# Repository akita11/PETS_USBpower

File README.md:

# PETS_USBpower

[PETS](https://4ok.jp/pets/)をUSBモバイルバッテリで使えるように改造する部品です。

※PETSを分解・改造して使用します。そのため、PETSの製品保証の対象外となります。

# 用意するもの

※モバイルバッテリ以外の部材はスイッチサイエンスで委託販売予定です

* 筐体の板（2枚）：MDF板（厚さ2.5mm）をレーザーカッター等でカットします。（PETS_USBpower: PDFとInkscape SVGで同一内容）

* USBコネクタ：出っ張りが少ないUSBコネクタ（基板）。USBpowerconn_gerber.zipを基板製造サービス等で製造します（板厚は2.0mmとするか、1.6mmのものに裏面に厚紙などをはさんで厚さを調整する）※ケーブルが根本から切れやすいのでグルーガン等で強化したほうがいいです

* 電源ケーブル：JSTのXHコネクタ(2p)＋10cm程度のケーブル ※[aitendo](http://www.aitendo.com)で売っていることがある

* ダイソーで500円売っているUSBモバイルバッテリ（またはそれと同等のサイズのもの）。サイズは120mm x 70mm x 20mm程度以下であれば、収まります。

# 組み立て

[こちらの手順](https://github.com/akita11/PETS_USBpower/blob/master/instruction/README.md)で、PETSを分解・改造します。改造後は、普段どおりのPETSとして使用できます。

# おまけ

PETSblock_holder.{svg/pdf}をダンボール等でカットして組み立てると、PETSのブロックを保存しておくのに使えます。

# Author

Junichi Akita / @akita11 / akita@ifdl.jp

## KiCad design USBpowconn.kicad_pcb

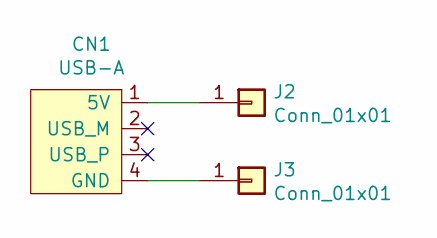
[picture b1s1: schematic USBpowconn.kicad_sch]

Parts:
CN1: USB-A; USB-A-PCB
J2, J3: Conn_01x01; PinSocket_1x01_P2.54mm_Vertical

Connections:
unnamed: CN1.1 (5V), J2.1
unnamed: CN1.4 (GND), J3.1

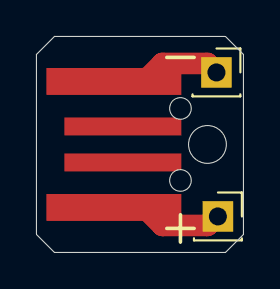
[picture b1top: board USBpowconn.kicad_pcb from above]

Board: 2 copper layers, 11.5 x 12.0 mm, 3 parts (0 on the bottom side), 2 nets.

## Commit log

2019-07-01 1st commit
2019-07-01 画像URLを修正
2021-03-05 README.mdも誤字を修正
2022-10-05 add instruction
2022-10-05 add block_holder
2022-10-09 add USB connector back
